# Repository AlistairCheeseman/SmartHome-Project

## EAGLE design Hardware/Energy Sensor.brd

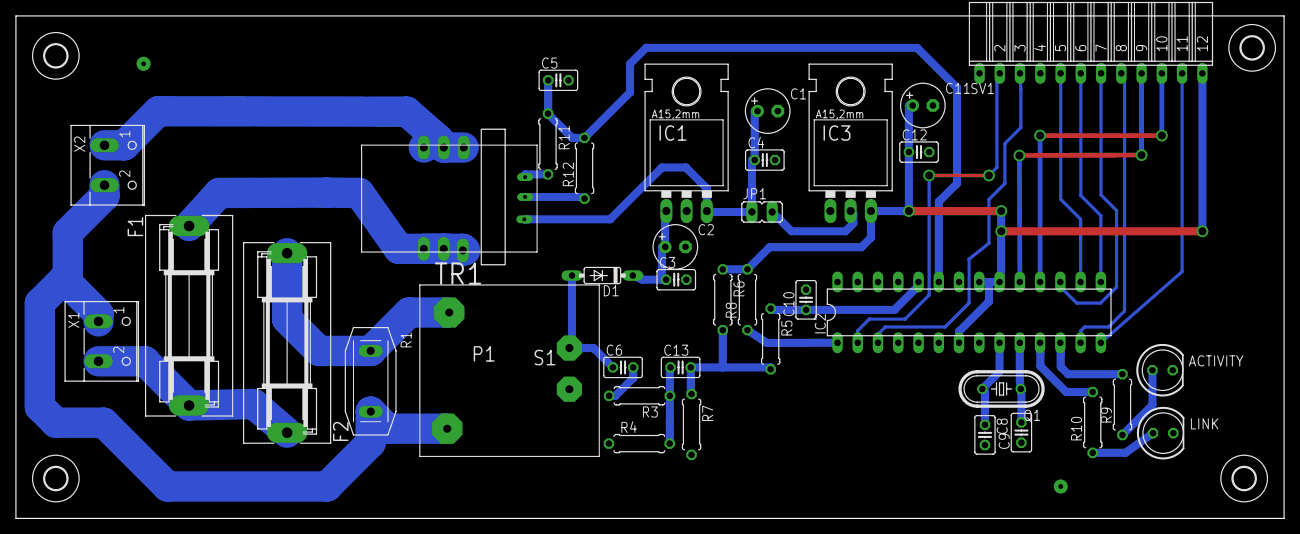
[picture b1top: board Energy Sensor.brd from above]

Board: 2 copper layers, 159.0 x 63.0 mm, 42 parts (0 on the bottom side), 33 nets.

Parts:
ACTIVITY: RED; LED5MM
C1, C11: 10u; E2,5-6
C2: 47u; E2,5-6
C3, C4, C12: 1n; C025-025X050
C5: 1p; C025-025X050
C6, C10, C13: 1u; C025-025X050
C8, C9: 22p; C025-025X050
D1: 1N4148DO35-7; DO35-7
F1: 230V 10A; SH22,5A
F2: 230V 100mA; SH22,5A
H1, H2, H3, H4: MOUNT-HOLE2.8; 2,8
IC1: 7805; 78XXL
IC2: ATMega328p-pu; DIL28-3
IC3: ld33v; 79XXL
JP1: Extern_Power; JP1
LINK: GRN; LED5MM
Q1: 16MHz; HC49/S
R1: P594
R3: 120K; 0207/7
R4: 10k; 0207/7
R5: 1k; 0207/7
R6, R7: 470k; 0207/7
R8: 10K; 0207/7
R9, R10: 330R; 0207/7
R11: 56k; 0207/7
R12: 68k; 0207/7
SV1: Comms; FE12W
TR1: vn20.10 09477; VV11
U$1: CAS25-NP; CAS
X1: MAINS IN; W237-102
X2: MAINS OUT; W237-102

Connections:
+3V3: C11.+, C12.1, IC2.7, IC2.20, IC2.21, IC3.OUT, R6.1, R8.2, SV1.12
+5V: C1.+, C4.1, IC1.OUT, JP1.1, U$1.13
CE: IC2.16, SV1.5
CSN: IC2.15, SV1.6
CSN2: IC2.14, SV1.11
CURRENT_SENSE: C5.1, IC2.23, R11.1, R12.2
GND: ACTIVITY.K, C1.-, C2.-, C3.2, C4.2, C5.2, C8.2, C9.1, C10.2, C11.-, C12.2, IC1.GND, IC2.8, IC2.22, IC3.GND, LINK.K, R4.1, R7.2, R12.1, SV1.4, TR1.7, U$1.12
INT: IC2.13, SV1.8
MISO: IC2.18, SV1.10
MOSI: IC2.17, SV1.7
unnamed: R1.1, TR1.5, X1.1, X2.2
unnamed: IC3.IN, JP1.2
unnamed: C6.2, R3.2
unnamed: C6.1, D1.A, TR1.9
unnamed: F1.1, U$1.1, U$1.2, U$1.3
unnamed: C2.+, C3.1, D1.C, IC1.IN
unnamed: U$1.8, U$1.9, U$1.10, X2.1
unnamed: C13.1, R3.1, R4.2
unnamed: C13.2, R5.2, R6.2, R7.1
unnamed: R11.2, U$1.11
unnamed: C8.1, IC2.9, Q1.2
unnamed: C9.2, IC2.10, Q1.1
unnamed: LINK.A, R10.1
unnamed: ACTIVITY.A, R9.1
unnamed: IC2.1, R8.1
unnamed: IC2.12, R9.2
unnamed: IC2.11, R10.2
unnamed: F2.2, R1.2, TR1.1
unnamed: F1.2, F2.1, X1.2
RXD: IC2.2, SV1.2
SCK: IC2.19, SV1.9
TXD: IC2.3, SV1.3
VSENSE: C10.1, IC2.24, R5.1

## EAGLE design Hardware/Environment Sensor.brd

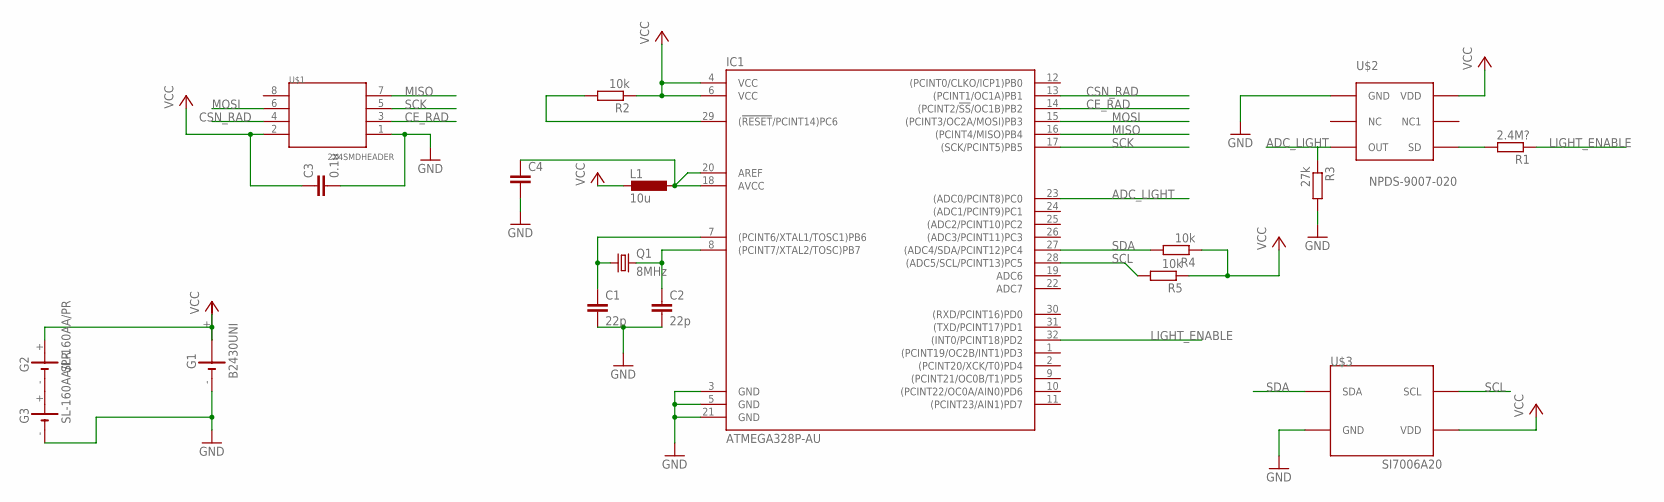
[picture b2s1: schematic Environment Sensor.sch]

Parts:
C1, C2: 22p; C1206K
C3: 0.1u; C1206K
C4: C-EUC1206; C1206
G1: B2430UNI
G2, G3: SL-160AA/PR
IC1: ATMEGA328P-AU; TQFP32-08
L1: 10u; L3216C
Q1: 8MHz; HC49UP
R1: 2.4M?; R1206
R2, R4, R5: 10k; R1206
R3: 27k; R1206
U$1: 2X4SMDHEADER; TSM-110-XX-XXX-DV
U$2: NPDS-9007-020; APDS-9007
U$3: SI7006A20; 3X3DFN

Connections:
ADC_LIGHT: IC1.23 ((ADC0/PCINT8)PC0), R3.1, U$2.P$3 (OUT)
CE_RAD: IC1.14 ((PCINT2/!SS!/OC1B)PB2), U$1.3
CSN_RAD: IC1.13 ((PCINT1/OC1A)PB1), U$1.4
GND: C1.2, C2.2, C3.2, C4.2, G1.-, G3.-, IC1.3 (GND), IC1.5 (GND), IC1.21 (GND), R3.2, U$1.1, U$2.P$1 (GND), U$3.P$2 (GND)
LIGHT_ENABLE: IC1.32 ((INT0/PCINT18)PD2), R1.1
MISO: IC1.16 ((PCINT4/MISO)PB4), U$1.7
MOSI: IC1.15 ((PCINT3/OC2A/MOSI)PB3), U$1.6
unnamed: C1.1, IC1.7 ((PCINT6/XTAL1/TOSC1)PB6), Q1.1
unnamed: C2.1, IC1.8 ((PCINT7/XTAL2/TOSC)PB7), Q1.2
unnamed: IC1.29 ((!RESET!/PCINT14)PC6), R2.2
unnamed: G2.-, G3.+
unnamed: R1.2, U$2.P$6 (SD)
unnamed: C4.1, IC1.18 (AVCC), IC1.20 (AREF), L1.1
SCK: IC1.17 ((SCK/PCINT5)PB5), U$1.5
SCL: IC1.28 ((ADC5/SCL/PCINT13)PC5), R5.2, U$3.P$6 (SCL)
SDA: IC1.27 ((ADC4/SDA/PCINT12)PC4), R4.2, U$3.P$1 (SDA)
VCC: C3.1, G1.+, G1.+@1 (+), G1.+@2 (+), G1.+@3 (+), G1.+@4 (+), G2.+, IC1.4 (VCC), IC1.6 (VCC), L1.2, R2.1, R4.1, R5.1, U$1.2, U$2.P$4 (VDD), U$3.P$5 (VDD)

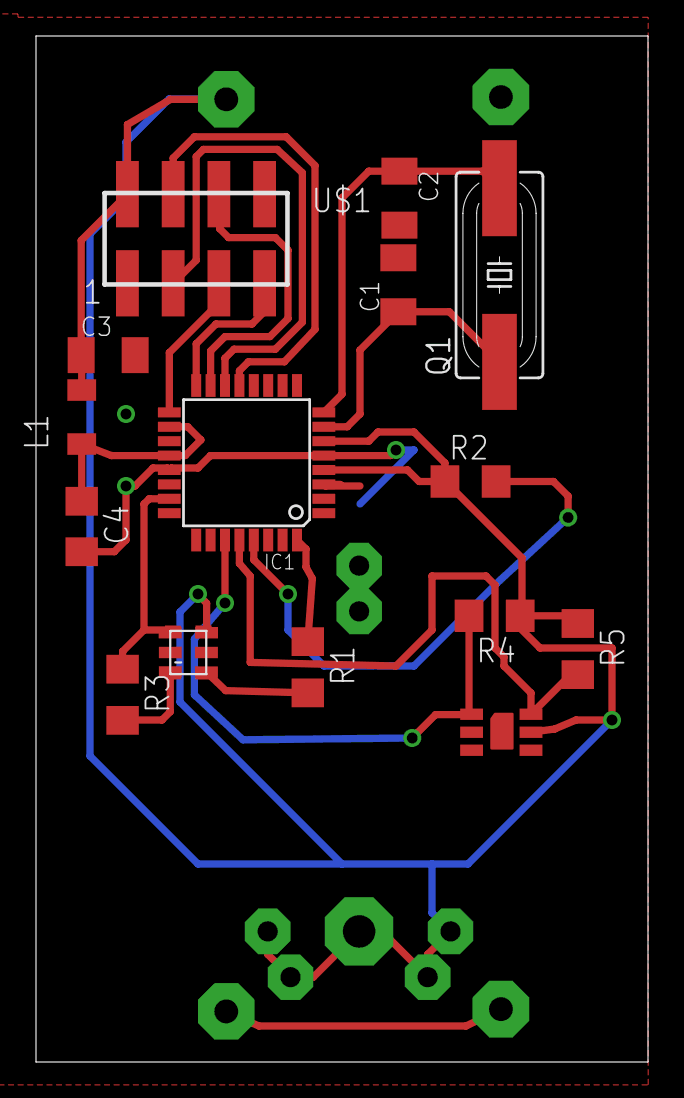
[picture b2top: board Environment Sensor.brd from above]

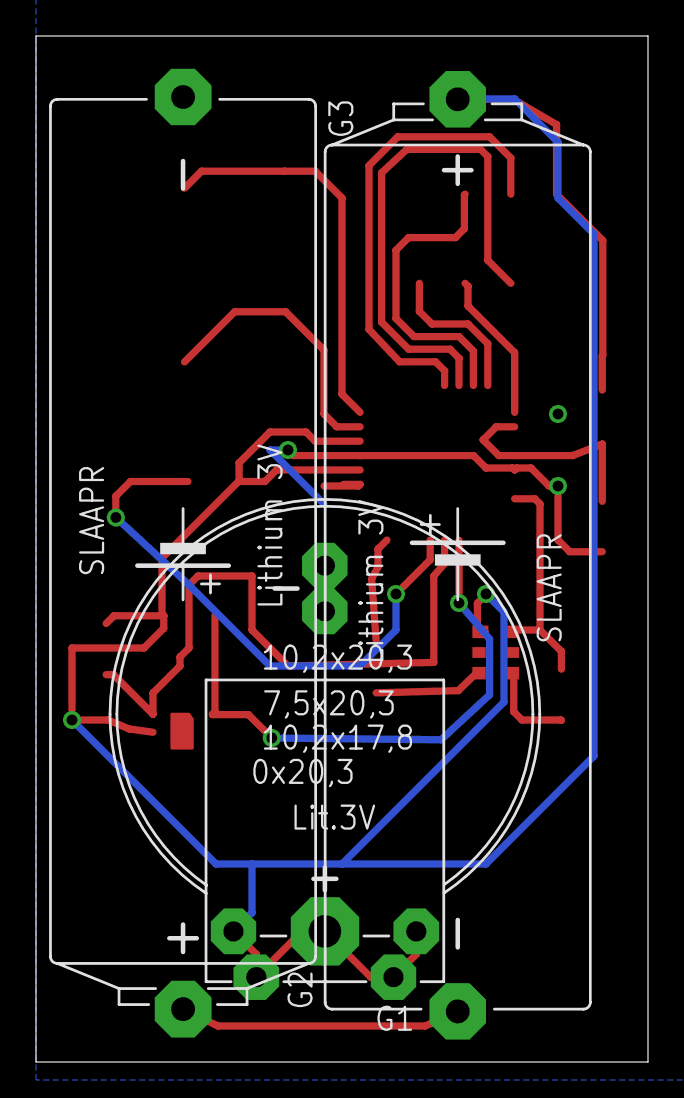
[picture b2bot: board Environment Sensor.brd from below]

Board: 2 copper layers, 34.0 x 57.0 mm, 18 parts (3 on the bottom side), 17 nets.

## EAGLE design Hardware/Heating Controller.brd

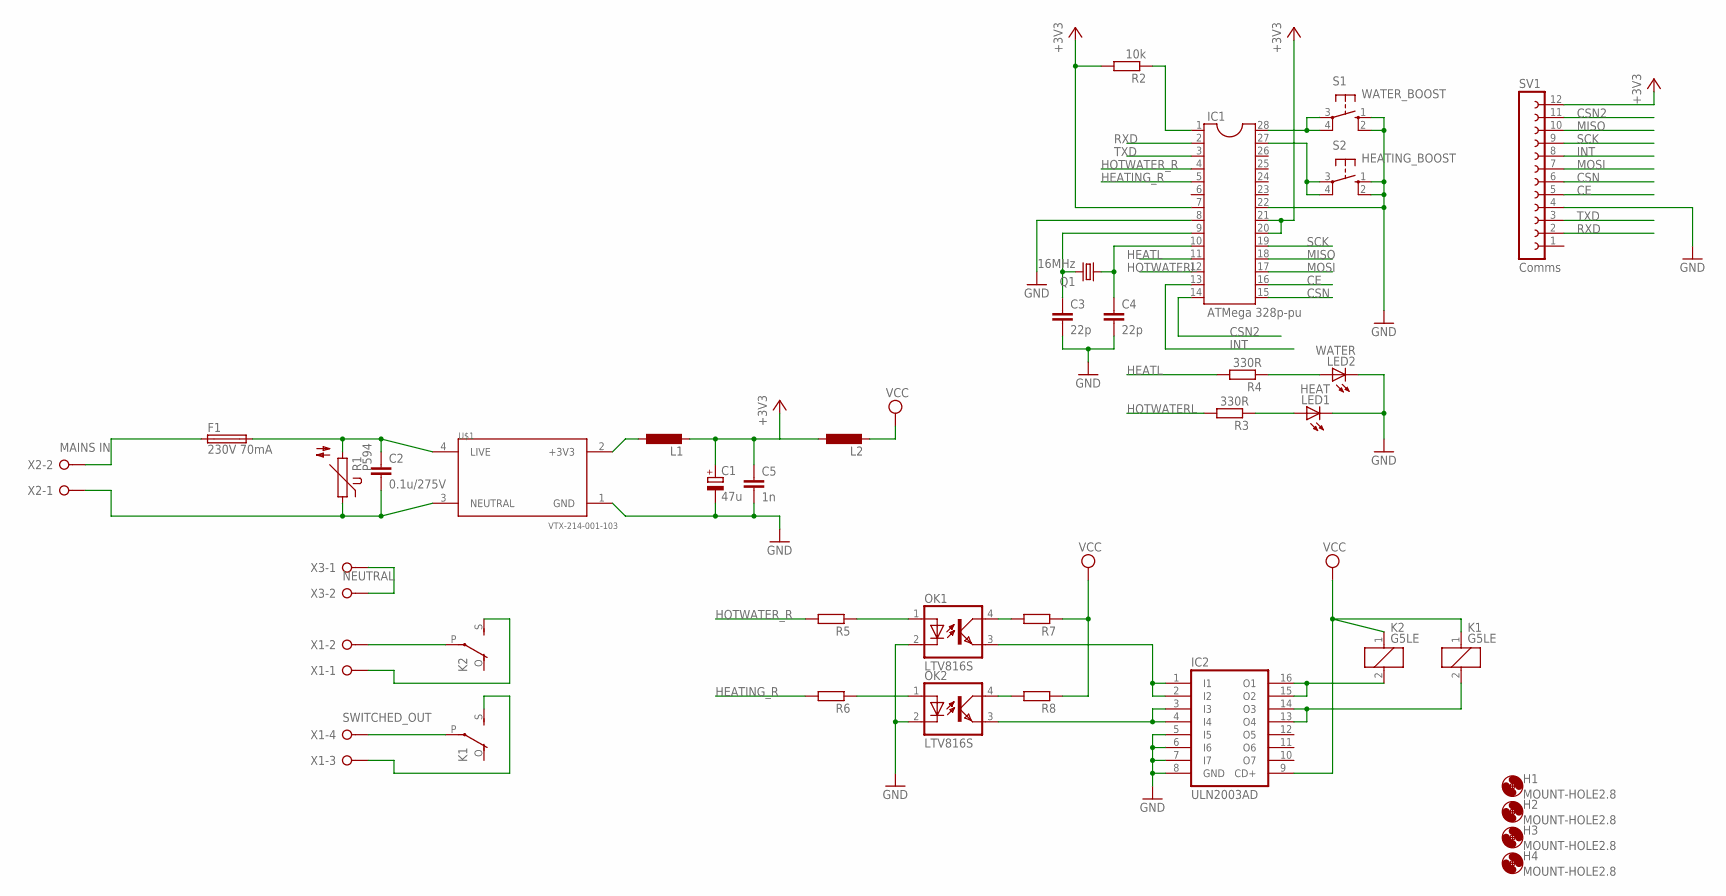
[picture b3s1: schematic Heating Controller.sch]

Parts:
C1: 47u; E2,5-7
C2: 0.1u/275V; C15B5
C3, C4: 22p; C1206K
C5: 1n; C1206K
F1: 230V 70mA; SH22,5A
H1, H2, H3, H4: MOUNT-HOLE2.8; 2,8
IC1: ATMega 328p-pu; DIL28-3
IC2: ULN2003AD; SO16
K1, K2: G5LE
L1, L2: L-EUL1812; L1812
LED1: HEAT; LED5MM
LED2: WATER; LED5MM
OK1, OK2: LTV816S; SMD4
Q1: 16MHz; HC49/S
R1: P594
R2: 10k; R1206W
R3, R4: 330R; R1206W
R5, R6, R7, R8: R-EU_R1206W; R1206W
S1: WATER_BOOST; B3F-40XX
S2: HEATING_BOOST; B3F-40XX
SV1: Comms; FE12W
U$1: VTX-214-001-103; VTX214001103
X1: SWITCHED_OUT; W237-4P
X2: MAINS IN; W237-132
X3: NEUTRAL; W237-132

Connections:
+3V3: C1.+, C5.1, IC1.7, IC1.20, IC1.21, L1.2, L2.1, R2.2, SV1.12
+3V3A: L1.1, U$1.2 (+3V3)
CE: IC1.16, SV1.5
CSN: IC1.15, SV1.6
CSN2: IC1.14, SV1.11
GND: C1.-, C3.2, C4.2, C5.2, IC1.8, IC1.22, IC2.5 (I5), IC2.6 (I6), IC2.7 (I7), IC2.8 (GND), LED1.K (C), LED2.K (C), OK1.2 (C), OK2.2 (C), S1.1 (S), S1.2 (S1), S2.1 (S), S2.2 (S1), SV1.4, U$1.1 (GND)
HEATING_R: IC1.5, R6.2
HEATL: IC1.11, R4.2
HOTWATERL: IC1.12, R3.2
HOTWATER_R: IC1.4, R5.2
INT: IC1.13, SV1.8
MISO: IC1.18, SV1.10
MOSI: IC1.17, SV1.7
unnamed: F1.1, X2.2
unnamed: C2.1, F1.2, R1.2, U$1.4 (LIVE)
unnamed: C2.2, R1.1, U$1.3 (NEUTRAL), X2.1
unnamed: IC1.1, R2.1
unnamed: C3.1, IC1.9, Q1.2
unnamed: C4.1, IC1.10, Q1.1
unnamed: LED1.A, R3.1
unnamed: LED2.A, R4.1
unnamed: IC1.28, S1.3, S1.4 (P1)
unnamed: IC1.27, S2.3, S2.4 (P1)
unnamed: OK1.1 (A), R5.1
unnamed: IC2.15 (O2), IC2.16 (O1), K2.2
unnamed: IC2.13 (O4), IC2.14 (O3), K1.2
unnamed: OK2.1 (A), R6.1
unnamed: K2.P, X1.2
unnamed: K2.S, X1.1
unnamed: K1.P, X1.4
unnamed: K1.S, X1.3
unnamed: X3.1, X3.2
unnamed: OK1.4 (COL), R7.2
unnamed: OK2.4 (COL), R8.2
unnamed: IC2.1 (I1), IC2.2 (I2), OK1.3 (EMIT)
unnamed: IC2.3 (I3), IC2.4 (I4), OK2.3 (EMIT)
RXD: IC1.2, SV1.2
SCK: IC1.19, SV1.9
TXD: IC1.3, SV1.3
VCC: IC2.9 (CD+), K1.1, K2.1, L2.2, R7.1, R8.1

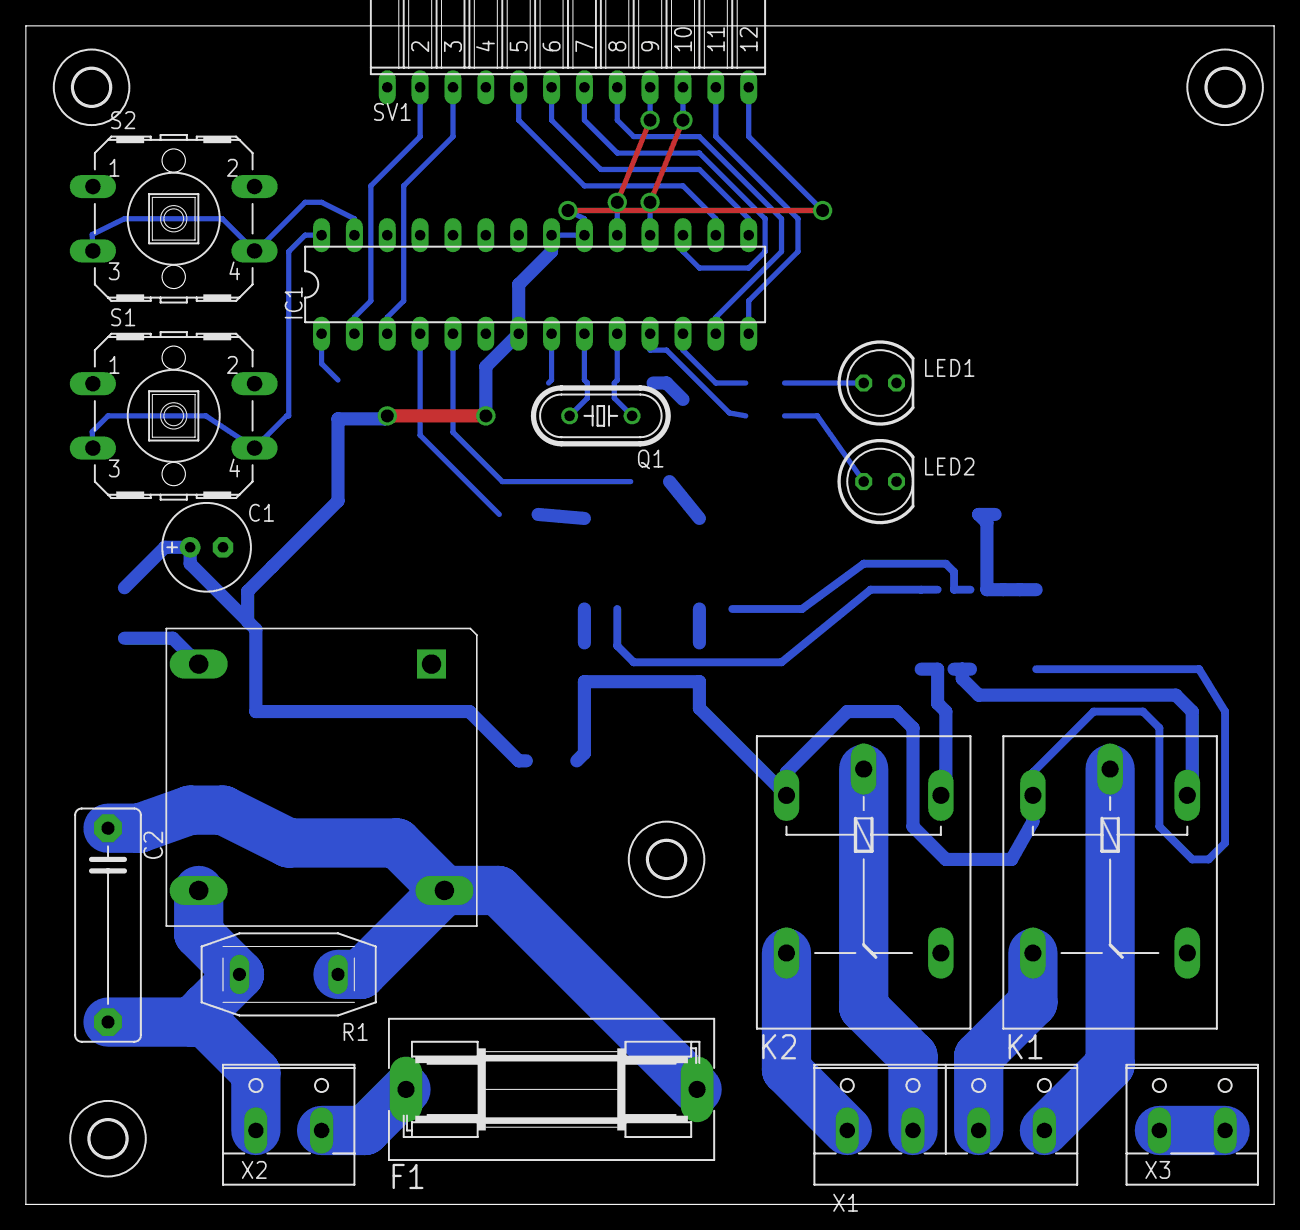
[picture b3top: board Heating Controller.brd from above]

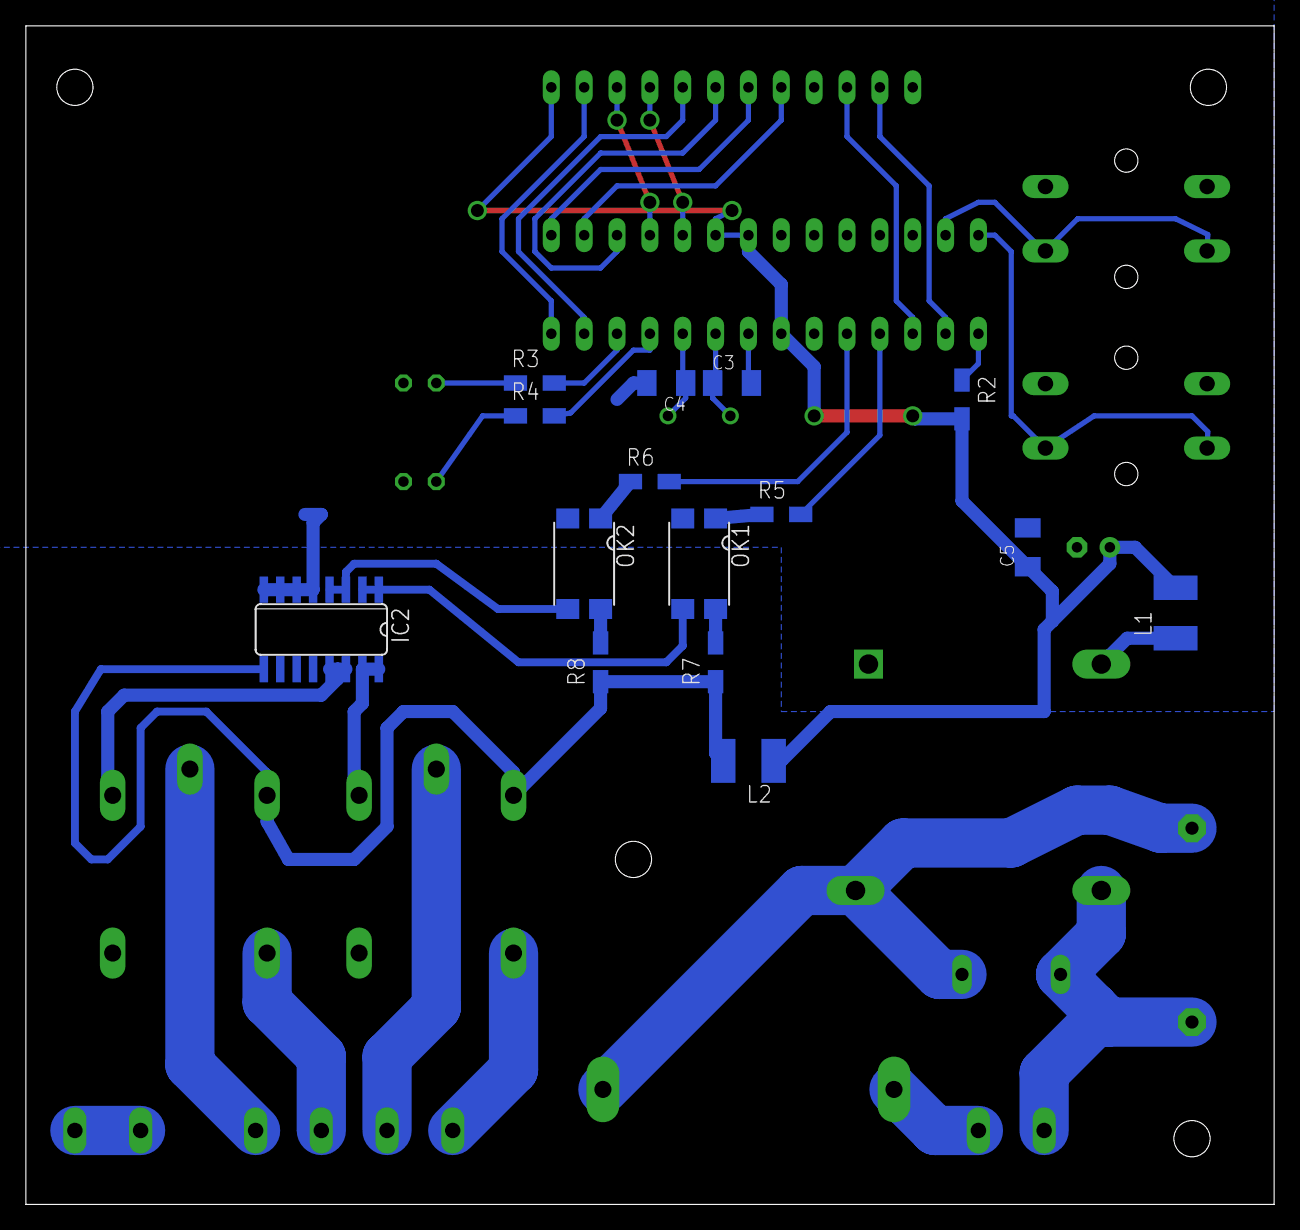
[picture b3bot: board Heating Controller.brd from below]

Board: 2 copper layers, 96.5 x 91.1 mm, 36 parts (15 on the bottom side), 40 nets.

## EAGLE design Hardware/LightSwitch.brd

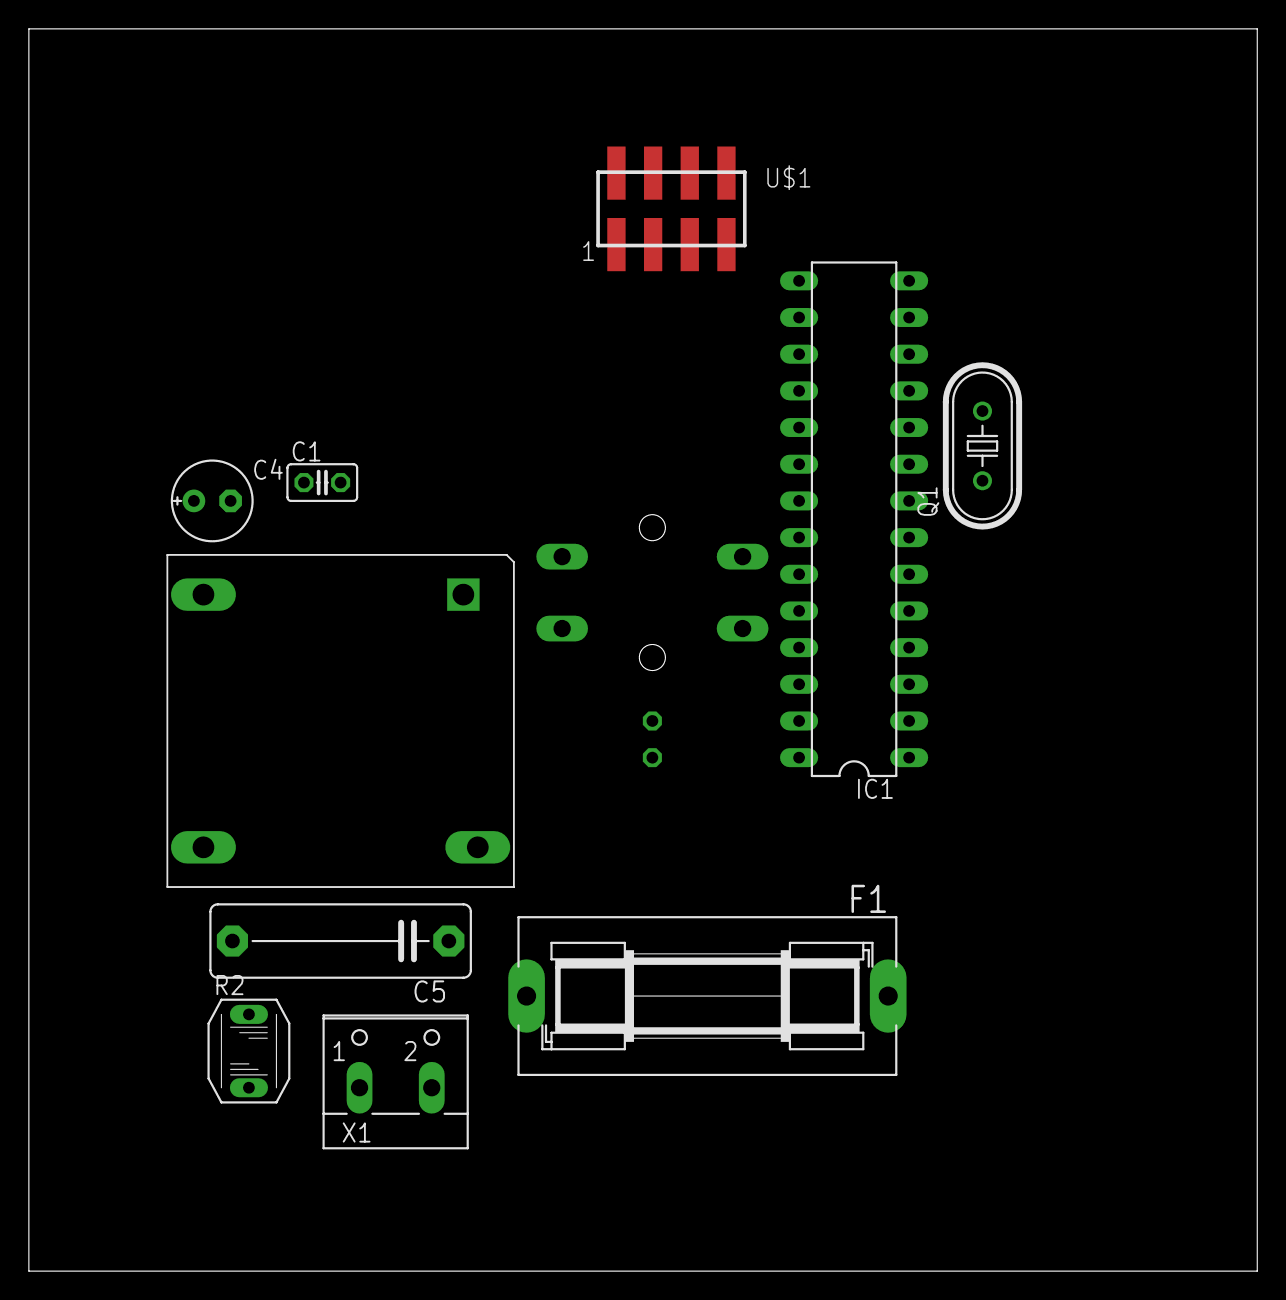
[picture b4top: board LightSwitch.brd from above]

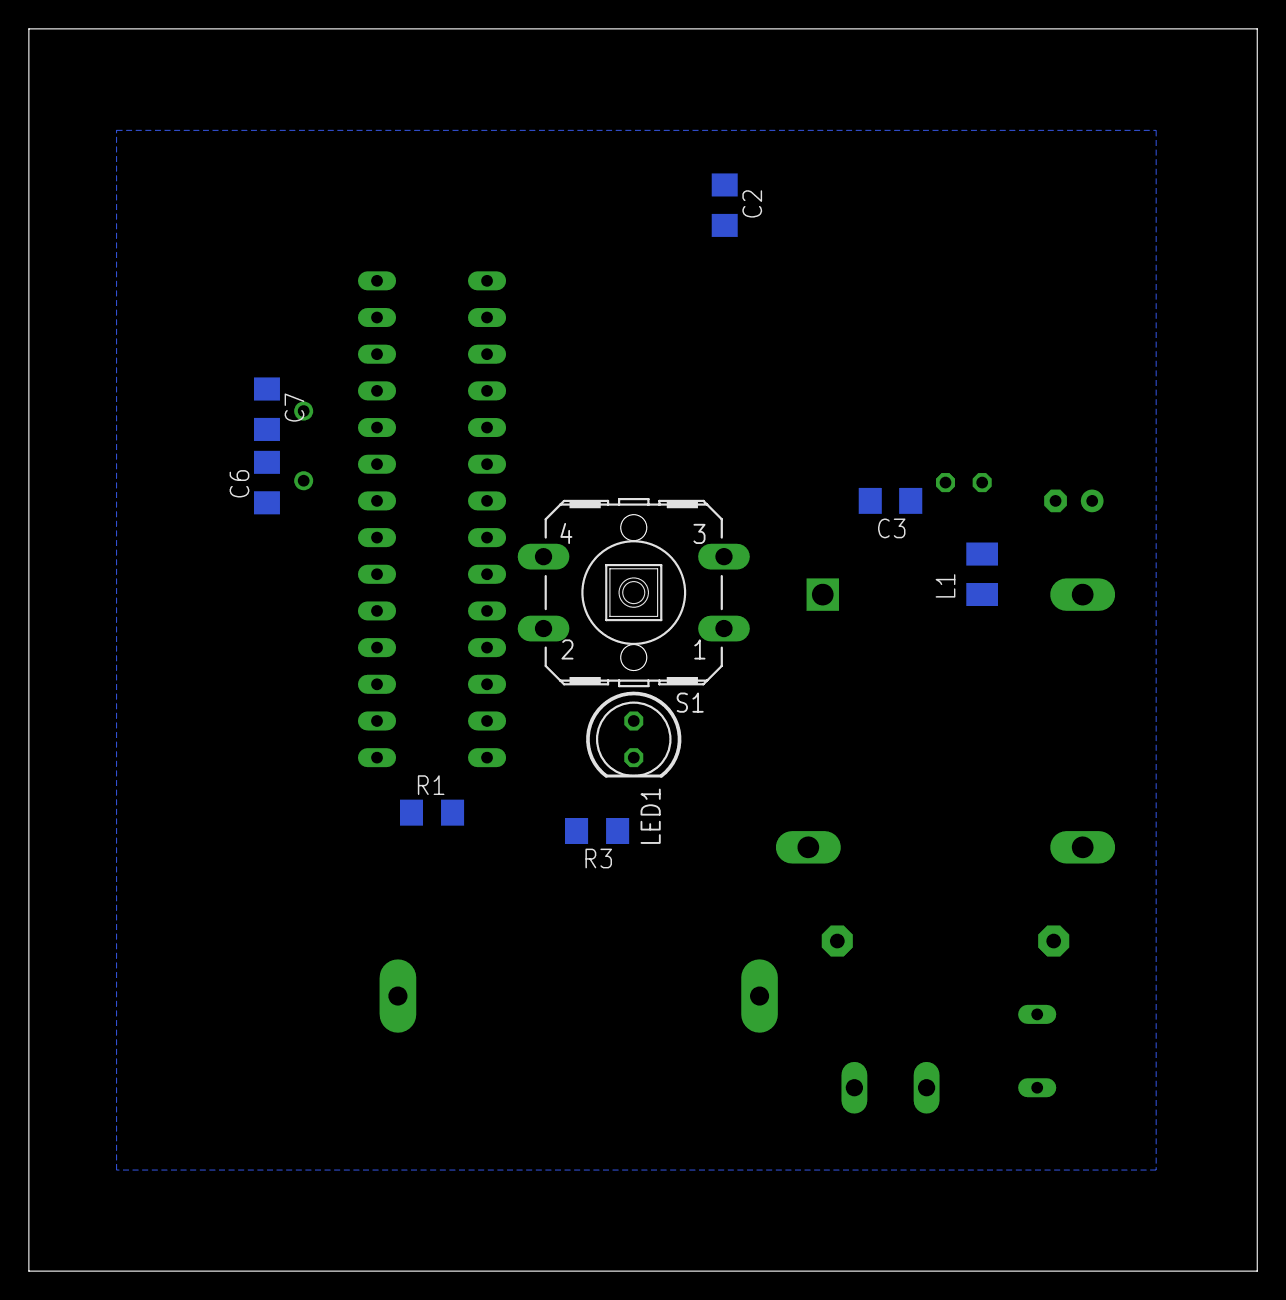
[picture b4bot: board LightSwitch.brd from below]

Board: 2 copper layers, 85.1 x 86.0 mm, 19 parts (9 on the bottom side), 17 nets, no tracks yet.

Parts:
C1: 1u; C025-025X050
C2: 1u; C1206
C3: 0.1u; C1206
C4: 47u; E2,5-6E
C5: 0.1u 275V; C15B5
C6, C7: 22p; C1206
F1: 70mA; SH25
IC1: ATMEGA328P; DIL28-3
L1: BEAD; L3230M
LED1: RED; LED5MM
Q1: 8MHz; HC49U70
R1: 10k; R1206
R2: P592
R3: 3k3; R1206
S1: SWITCH; B3F-40XX
U$1: 2X4SMDHEADER; TSM-110-XX-XXX-DV
U$2: VTX-214-001-103; VTX214001103
X1: MAINS; W237-102

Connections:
+3V3: C1.1, C2.1, C3.1, C4.+, IC1.7, IC1.20, L1.2, R1.2, U$1.2
CE_RAD: IC1.16, U$1.3
CSN_RAD: IC1.15, U$1.4
GND: C1.2, C2.2, C3.2, C4.-, C6.2, C7.2, IC1.8, IC1.21, IC1.22, LED1.K, S1.3, S1.4, U$1.1, U$2.1
MISO: IC1.18, U$1.7
MOSI: IC1.17, U$1.6
unnamed: F1.1, X1.1
unnamed: C5.1, F1.2, R2.2, U$2.4
unnamed: IC1.1, R1.1
unnamed: C5.2, R2.1, U$2.3, X1.2
unnamed: IC1.11, R3.2
unnamed: LED1.A, R3.1
unnamed: IC1.28, S1.1, S1.2
unnamed: C6.1, IC1.9, Q1.1
unnamed: C7.1, IC1.10, Q1.2
SCK: IC1.19, U$1.5
VOUT: L1.1, U$2.2
